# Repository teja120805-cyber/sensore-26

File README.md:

# PaveSight Edge Pipeline (Raspberry Pi + USB webcam)

Captures webcam frames on the Pi, runs your trained YOLOv8 pothole-detection
model, computes a severity score from the bounding box, tags the detection
with a position, and POSTs it to the PaveSight backend
(`POST /api/v1/detections`, matching `web-app-build-prompt.md`'s schema exactly).

## Current placeholders (by design, not bugs)

- **GPS/altitude**: `edge/geo.py` returns a fixed lat/lon/height from
  `edge/config.py` for every detection. Your Pixhawk's GPS module isn't
  integrated yet — `geo.py`'s docstring has the exact pymavlink code to drop
  in once it is. Nothing else in the pipeline needs to change when you do.
- **Camera intrinsics**: `SENSOR_WIDTH_MM` / `FOCAL_LENGTH_MM` in
  `edge/config.py` are placeholder values for a generic webcam. See
  "Calibrating without datasheet specs" below.

## Setup on the Pi

```bash
python3 -m venv venv
source venv/bin/activate
pip install -r requirements.txt
```

Drop your trained weights at `models/pothole_yolov8n.pt` (or update
`MODEL_PATH` in `edge/config.py` to point elsewhere).

Edit `edge/config.py`:
- `CAMERA_INDEX` — confirm with `ls /dev/video*`
- `BACKEND_URL` — the LAN IP of the laptop running the backend, e.g.
  `http://192.168.1.50:8000/api/v1/detections` (find it with `ipconfig` on
  the laptop; make sure the Pi and laptop are on the same WiFi network and
  the backend's Docker Compose port 8000 is exposed, not just bound to
  localhost)

## Run it

```bash
python -m edge.main
```

You should see `[uploader] detection uploaded` in the console each time a
pothole is detected and successfully sent. If the backend is unreachable,
detections are queued to `offline_queue.jsonl` and retried automatically
once it's back.

## Run it on boot (optional, for a live demo)

```bash
sudo cp systemd/pavesight-edge.service /etc/systemd/system/
sudo systemctl daemon-reload
sudo systemctl enable --now pavesight-edge
journalctl -u pavesight-edge -f   # watch logs
```

Update the `WorkingDirectory` path in the service file first if you didn't
clone this to `/home/pi/pavesight-edge`.

## Calibrating without datasheet specs

If you don't know your webcam's exact sensor width / focal length:

1. Place an object of known width (e.g. a ruler, 0.30 m) flat on the ground.
2. Mount the camera at your real `CAMERA_HEIGHT_M` and capture a frame.
3. Measure the object's width in pixels in that frame.
4. Compute meters-per-pixel directly: `known_width_m / width_px`.
5. Back out an equivalent `SENSOR_WIDTH_MM` so
   `ground_sample_distance_m_per_px()` in `edge/severity.py` reproduces that
   value — or simplest: replace that function's body with your measured
   meters-per-pixel constant divided by `CAMERA_HEIGHT_M` and scale linearly
   with height. Either way, re-measure if you change camera height.

## Testing against the backend without a Pi

You can validate the payload shape hits the backend correctly with `curl`,
using the same JSON shape `main.py` builds:

```bash
curl -X POST http://<backend-ip>:8000/api/v1/detections \
  -H "Content-Type: application/json" \
  -d '{
    "timestamp": "2026-09-16T10:42:11Z",
    "lat": 12.971599,
    "lon": 77.594566,
    "altitude_m": 1.2,
    "severity": "medium",
    "confidence": 0.83,
    "area_m2": 0.14,
    "defect_class": "pothole",
    "image_base64": ""
  }'
```

## Performance note (Raspberry Pi 4)

`ultralytics` pulls in PyTorch, which is heavy for a Pi 4's CPU. YOLOv8n
should still run at a few FPS, enough for a walking-pace or slow-vehicle
demo. If you need more speed, export your model to ONNX
(`model.export(format="onnx")` from ultralytics) and swap `detector.py` to
run inference via `cv2.dnn.readNetFromONNX` instead — same interface, no
PyTorch dependency, noticeably faster on Pi CPUs.

## Not in scope here

- MAVLink/Pixhawk GPS integration (placeholder in `geo.py`, wire in when the
  GPS module is ready)
- Any drone flight logic — this assumes a Pi + webcam set up for detection
  only, matching how you described this pass

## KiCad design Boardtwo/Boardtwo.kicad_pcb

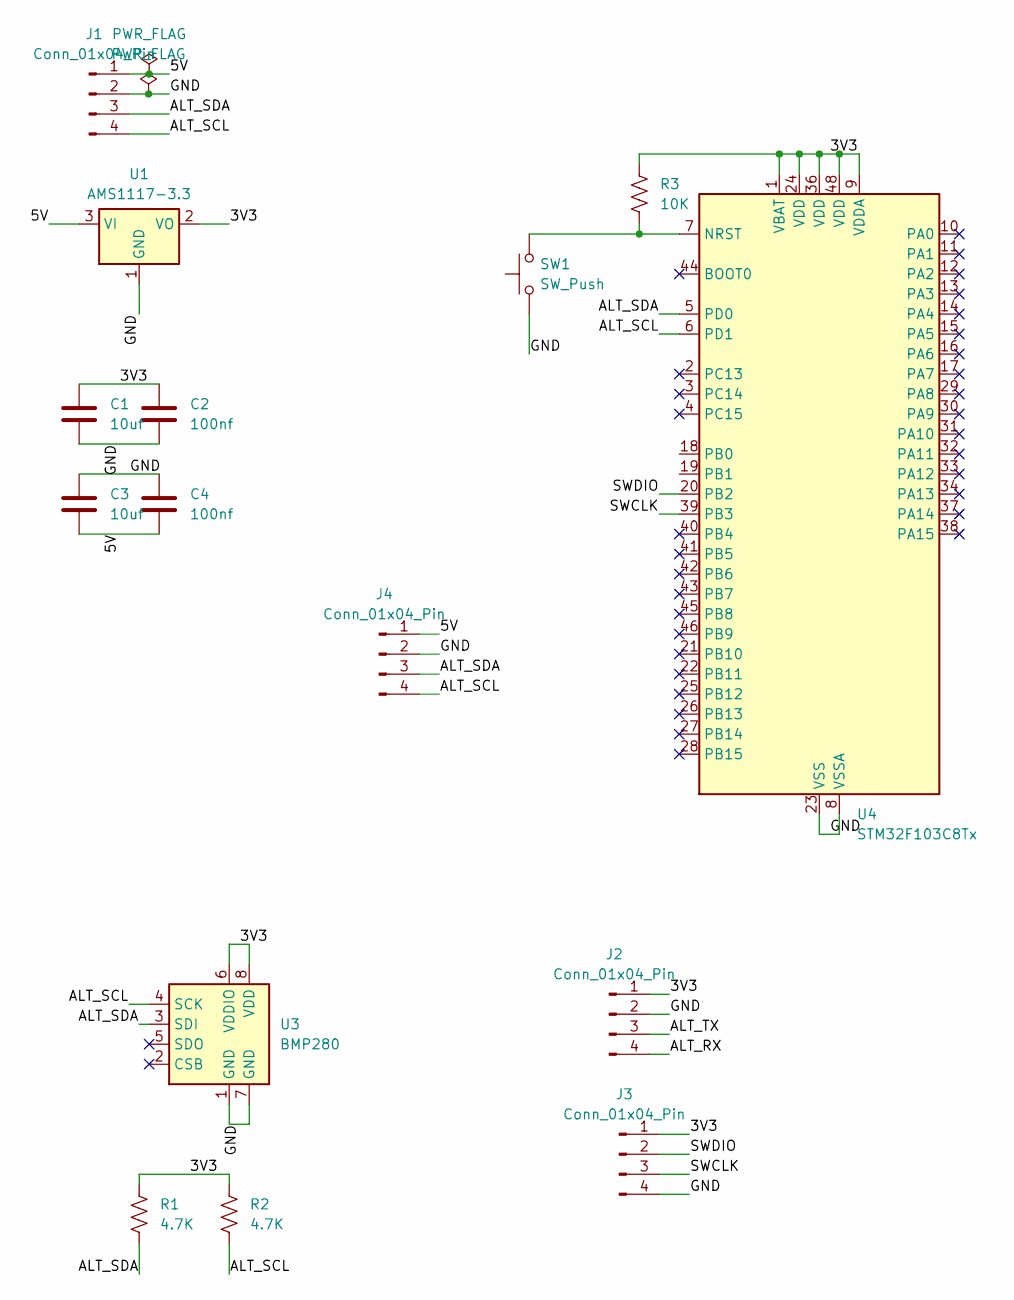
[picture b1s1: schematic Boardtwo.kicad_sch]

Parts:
C1, C3: 10uf; C_0603_1608Metric_Pad1.08x0.95mm_HandSolder
C2, C4: 100nf; C_0603_1608Metric_Pad1.08x0.95mm_HandSolder
J1, J2, J3, J4: Conn_01x04_Pin; PinHeader_1x04_P2.54mm_Vertical
R1, R2: 4.7K; R_0603_1608Metric_Pad0.98x0.95mm_HandSolder
R3: 10K; R_0603_1608Metric_Pad0.98x0.95mm_HandSolder
SW1: SW_Push; SW_BUTT-2
U1: AMS1117-3.3; SOT-223-3_TabPin2
U3: BMP280; Bosch_LGA-8_2x2.5mm_P0.65mm_ClockwisePinNumbering
U4: STM32F103C8Tx; LQFP-48_7x7mm_P0.5mm

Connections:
/3V3: C1.1, C2.1, J2.1, J3.1, R1.1, R2.1, R3.1, U1.2 (VO), U3.6 (VDDIO), U3.8 (VDD), U4.1 (VBAT), U4.9 (VDDA), U4.24 (VDD), U4.36 (VDD), U4.48 (VDD)
/5V: C3.2, C4.2, J1.1, J4.1, U1.3 (VI)
/ALT_RX: J2.4
/ALT_SCL: J1.4, J4.4, R2.2, U3.4 (SCK), U4.6 (PD1)
/ALT_SDA: J1.3, J4.3, R1.2, U3.3 (SDI), U4.5 (PD0)
/ALT_TX: J2.3
/GND: C1.2, C2.2, C3.1, C4.1, J1.2, J2.2, J3.4, J4.2, SW1.1, U1.1 (GND), U3.1 (GND), U3.7 (GND), U4.8 (VSSA), U4.23 (VSS), U4.35 (VSS), U4.47 (VSS)
/SWCLK: J3.3, U4.39 (PB3)
/SWDIO: J3.2, U4.20 (PB2)
unnamed: R3.2, SW1.2, U4.7 (NRST)

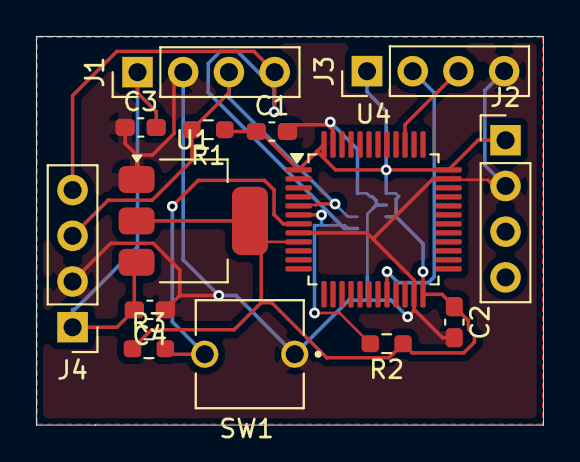
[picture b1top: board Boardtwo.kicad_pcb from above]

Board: 2 copper layers, 28.2 x 21.6 mm, 15 parts (1 on the bottom side), 8 nets.

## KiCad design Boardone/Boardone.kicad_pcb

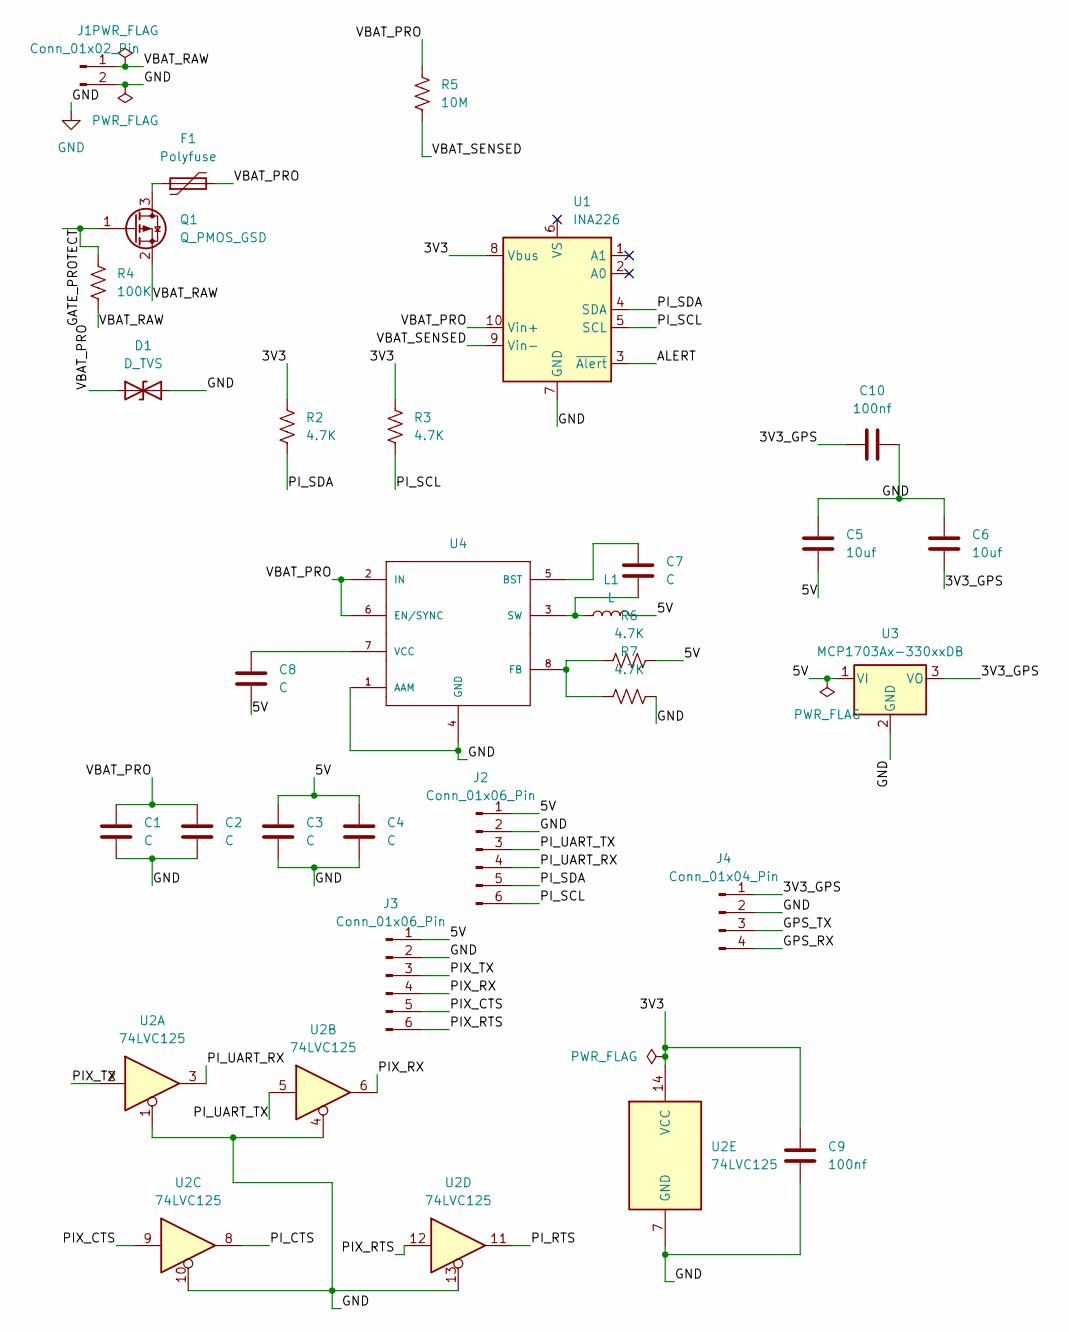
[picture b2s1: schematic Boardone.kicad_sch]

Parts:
C1, C2, C3, C4, C7, C8: C; C_0603_1608Metric_Pad1.08x0.95mm_HandSolder
C5, C6: 10uf; C_0603_1608Metric_Pad1.08x0.95mm_HandSolder
C9, C10: 100nf; C_0603_1608Metric_Pad1.08x0.95mm_HandSolder
D1: D_TVS; R_0603_1608Metric_Pad0.98x0.95mm_HandSolder
F1: Polyfuse; R_0603_1608Metric_Pad0.98x0.95mm_HandSolder
J1: Conn_01x02_Pin; PinHeader_1x02_P2.54mm_Vertical
J2, J3: Conn_01x06_Pin; PinHeader_1x06_P2.54mm_Vertical
J4: Conn_01x04_Pin; PinHeader_1x04_P2.54mm_Vertical
L1: L; L_0603_1608Metric_Pad1.05x0.95mm_HandSolder
Q1: Q_PMOS_GSD; SOT-223-3_TabPin2
R2, R3, R6, R7: 4.7K; R_0603_1608Metric_Pad0.98x0.95mm_HandSolder
R4: 100K; R_0603_1608Metric_Pad0.98x0.95mm_HandSolder
R5: 10M; R_0603_1608Metric_Pad0.98x0.95mm_HandSolder
U1: INA226; TSSOP-10_3x3mm_P0.5mm
U2: 74LVC125; SOIC127P600X175-14N
U3: MCP1703Ax-330xxDB; SOT-223-3_TabPin2
U4: MP2315GJ; SOT-23-8; MPN MP2315

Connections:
/3V3: C9.1, R2.1, R3.1, U1.8 (Vbus), U2.14 (VCC)
/3V3_GPS: C6.2, C10.1, J4.1, U3.3 (VO)
/5V: C3.1, C4.1, C5.2, C8.2, J2.1, J3.1, L1.2, R6.2, U3.1 (VI)
/ALERT: U1.3 (~Alert)
/GATE_PROTECT: Q1.1 (G), R4.1
/GPS_RX: J4.4
/GPS_TX: J4.3
/PIX_CTS: J3.5, U2.9
/PIX_RTS: J3.6, U2.12
/PIX_RX: J3.4, U2.6
/PIX_TX: J3.3, U2.2
/PI_CTS: U2.8
/PI_RTS: U2.11
/PI_SCL: J2.6, R3.2, U1.5 (SCL)
/PI_SDA: J2.5, R2.2, U1.4 (SDA)
/PI_UART_RX: J2.4, U2.3
/PI_UART_TX: J2.3, U2.5
/VBAT_PRO: C1.1, C2.1, D1.1 (A1), F1.2, R5.1, U1.10 (Vin+), U4.2 (IN), U4.6 (EN/SYNC)
/VBAT_RAW: J1.1, Q1.2 (S), R4.2
/VBAT_SENSED: R5.2, U1.9 (Vin-)
GND: C1.2, C2.2, C3.2, C4.2, C5.1, C6.1, C9.2, C10.2, D1.2 (A2), J1.2, J2.2, J3.2, J4.2, R7.1, U1.7 (GND), U2.1, U2.4, U2.7 (GND), U2.10, U2.13, U3.2 (GND), U4.1 (AAM), U4.4 (GND)
unnamed: F1.1, Q1.3 (D)
unnamed: C7.1, U4.5 (BST)
unnamed: R6.1, R7.2, U4.8 (FB)
unnamed: C7.2, L1.1, U4.3 (SW)
unnamed: C8.1, U4.7 (VCC)

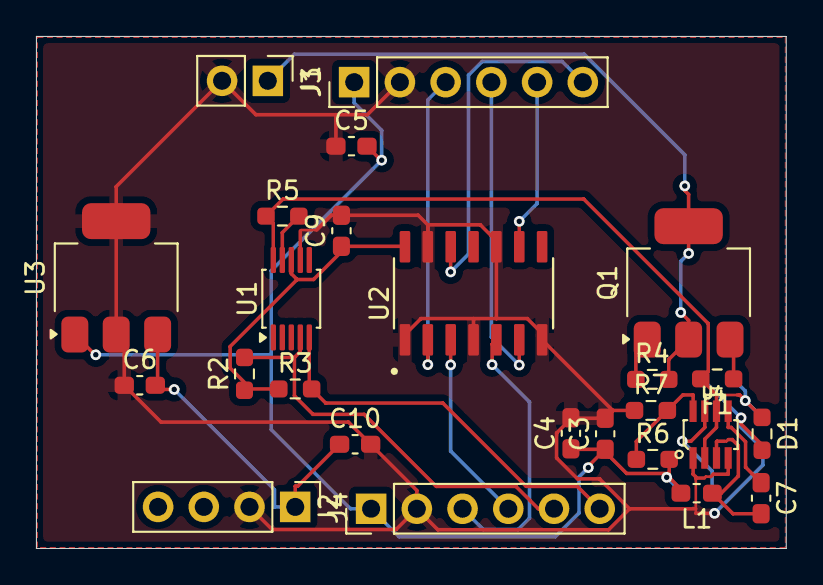
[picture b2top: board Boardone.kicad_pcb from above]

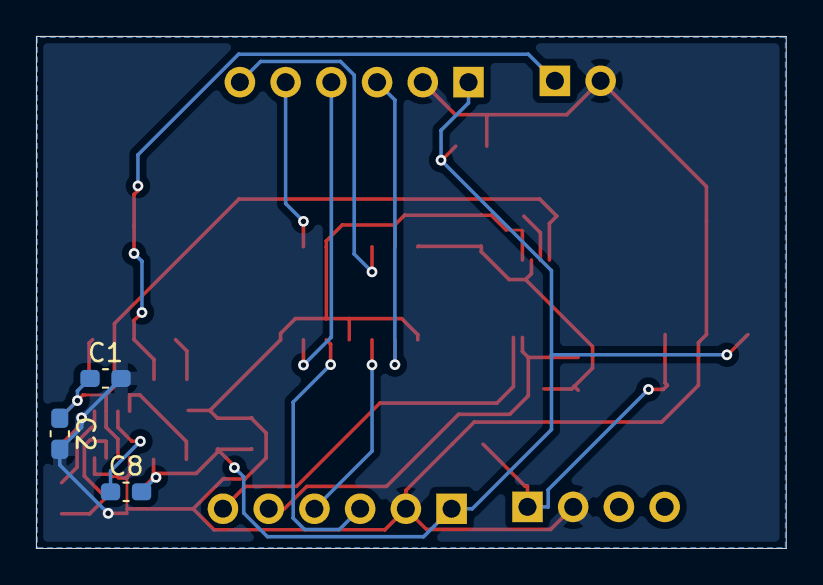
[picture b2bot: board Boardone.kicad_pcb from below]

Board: 2 copper layers, 41.7 x 28.4 mm, 28 parts (3 on the bottom side), 21 nets.
